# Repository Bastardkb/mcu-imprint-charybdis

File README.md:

# mcu-imprint-charybdis

Outdated, use https://github.com/Bastardkb/Elite-C-holder rev2

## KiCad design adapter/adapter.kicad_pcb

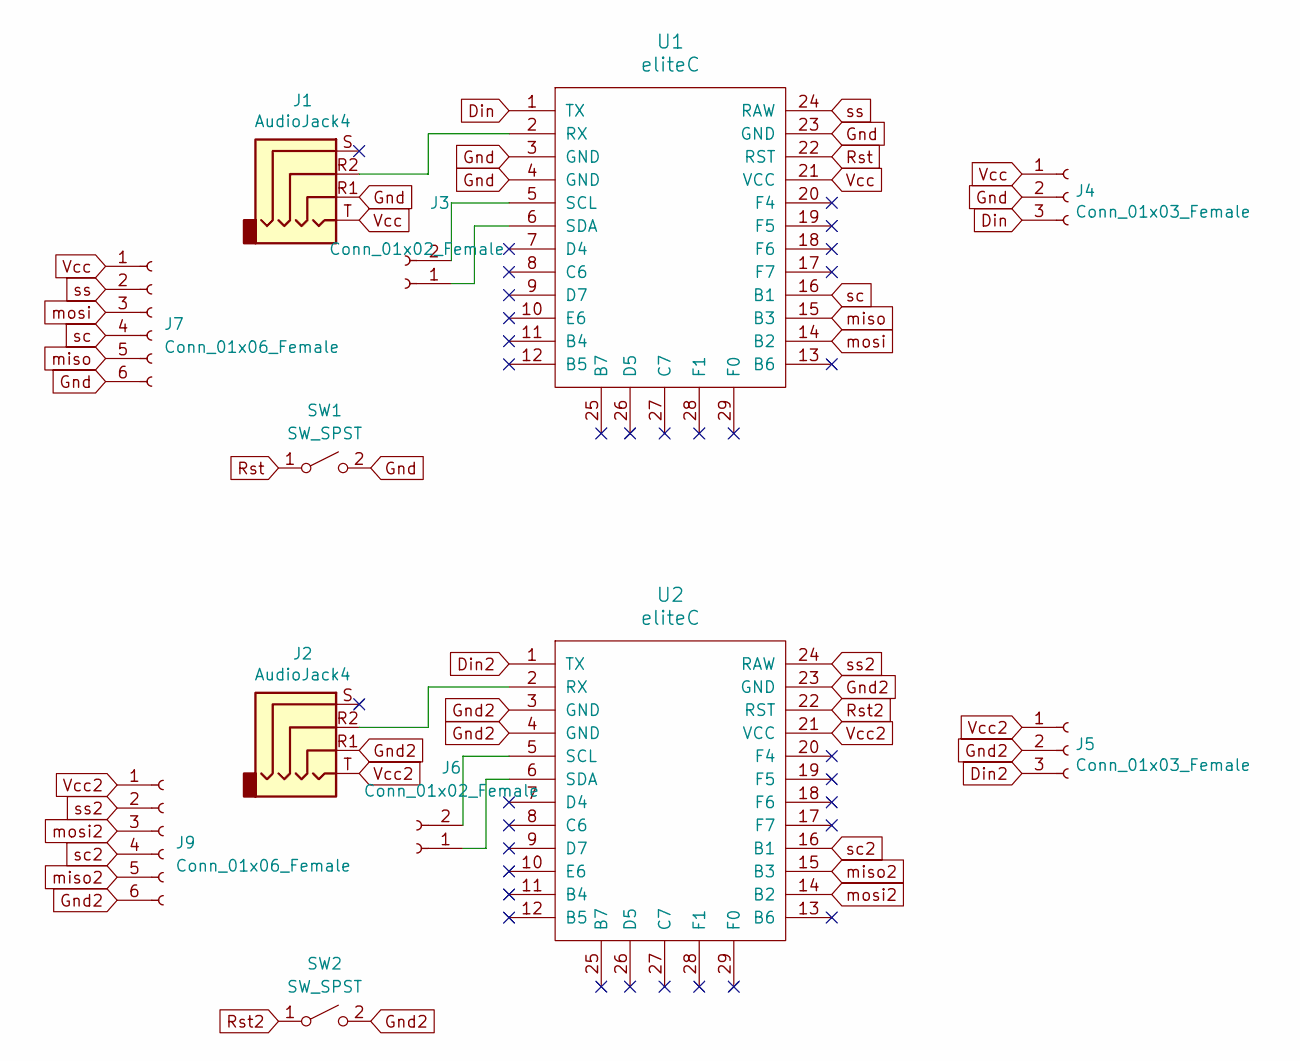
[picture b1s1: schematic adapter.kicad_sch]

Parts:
J1, J2: AudioJack4; Jack_3.5mm_PJ320E_Horizontal
J3, J6: Conn_01x02_Female; PinSocket_2x01_P2.54mm_Vertical
J4, J5: Conn_01x03_Female; PinSocket_1x03_P2.54mm_Vertical
J7, J9: Conn_01x06_Female; PinHeader_1x06_P2.54mm_Vertical
SW1, SW2: SW_SPST; switch_rst
U1, U2: eliteC; Elite-C-castellated-29pin-holes

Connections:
Din: J4.3, U1.1 (TX)
Din2: J5.3, U2.1 (TX)
Gnd: J1.R1, J4.2, J7.6, SW1.2 (B), U1.3 (GND), U1.4 (GND), U1.23 (GND)
Gnd2: J2.R1, J5.2, J9.6, SW2.2 (B), U2.3 (GND), U2.4 (GND), U2.23 (GND)
unnamed: J1.R2, U1.2 (RX)
unnamed: J2.R2, U2.2 (RX)
unnamed: J3.1, U1.6 (SDA)
unnamed: J3.2, U1.5 (SCL)
unnamed: J6.1, U2.6 (SDA)
unnamed: J6.2, U2.5 (SCL)
Rst: SW1.1 (A), U1.22 (RST)
Rst2: SW2.1 (A), U2.22 (RST)
Vcc: J1.T, J4.1, J7.1, U1.21 (VCC)
Vcc2: J2.T, J5.1, J9.1, U2.21 (VCC)
miso: J7.5, U1.15 (B3)
miso2: J9.5, U2.15 (B3)
mosi: J7.3, U1.14 (B2)
mosi2: J9.3, U2.14 (B2)
sc: J7.4, U1.16 (B1)
sc2: J9.4, U2.16 (B1)
ss: J7.2, U1.24 (RAW)
ss2: J9.2, U2.24 (RAW)

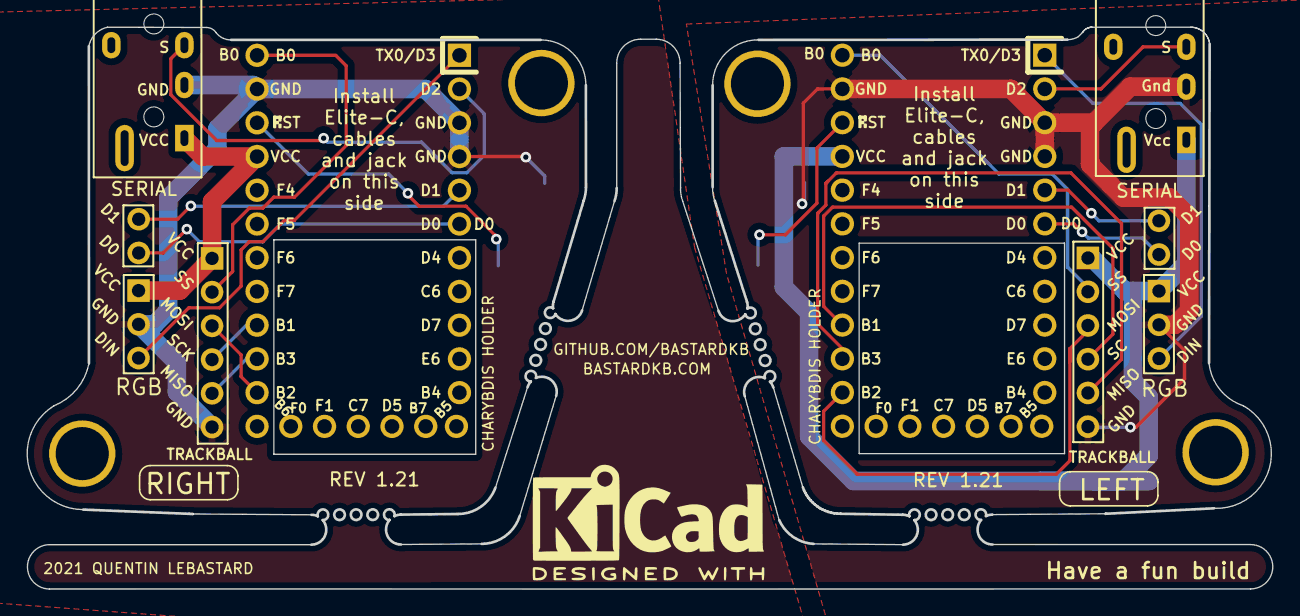
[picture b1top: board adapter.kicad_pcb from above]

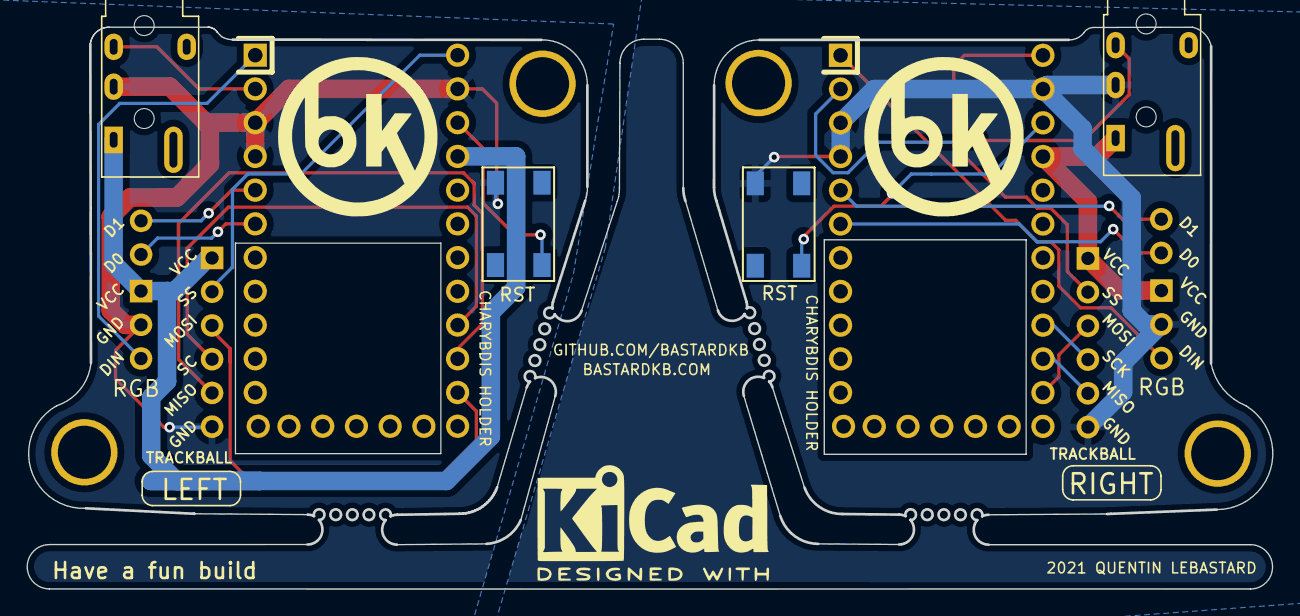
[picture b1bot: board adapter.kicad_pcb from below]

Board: 2 copper layers, 93.8 x 42.3 mm, 12 parts (6 on the bottom side), 22 nets.

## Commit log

2021-06-11 add everything
2021-06-11 left adapter
2021-06-11 routing
2021-06-11 silkscreen
2021-09-01 Remove ignored files
2021-09-19 slikscreen
